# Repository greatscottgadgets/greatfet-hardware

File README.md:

# GreatFET Hardware

This repository is deprecated.  Please use the current GreatFET hardware design repositories located at:

https://github.com/greatfet-hardware

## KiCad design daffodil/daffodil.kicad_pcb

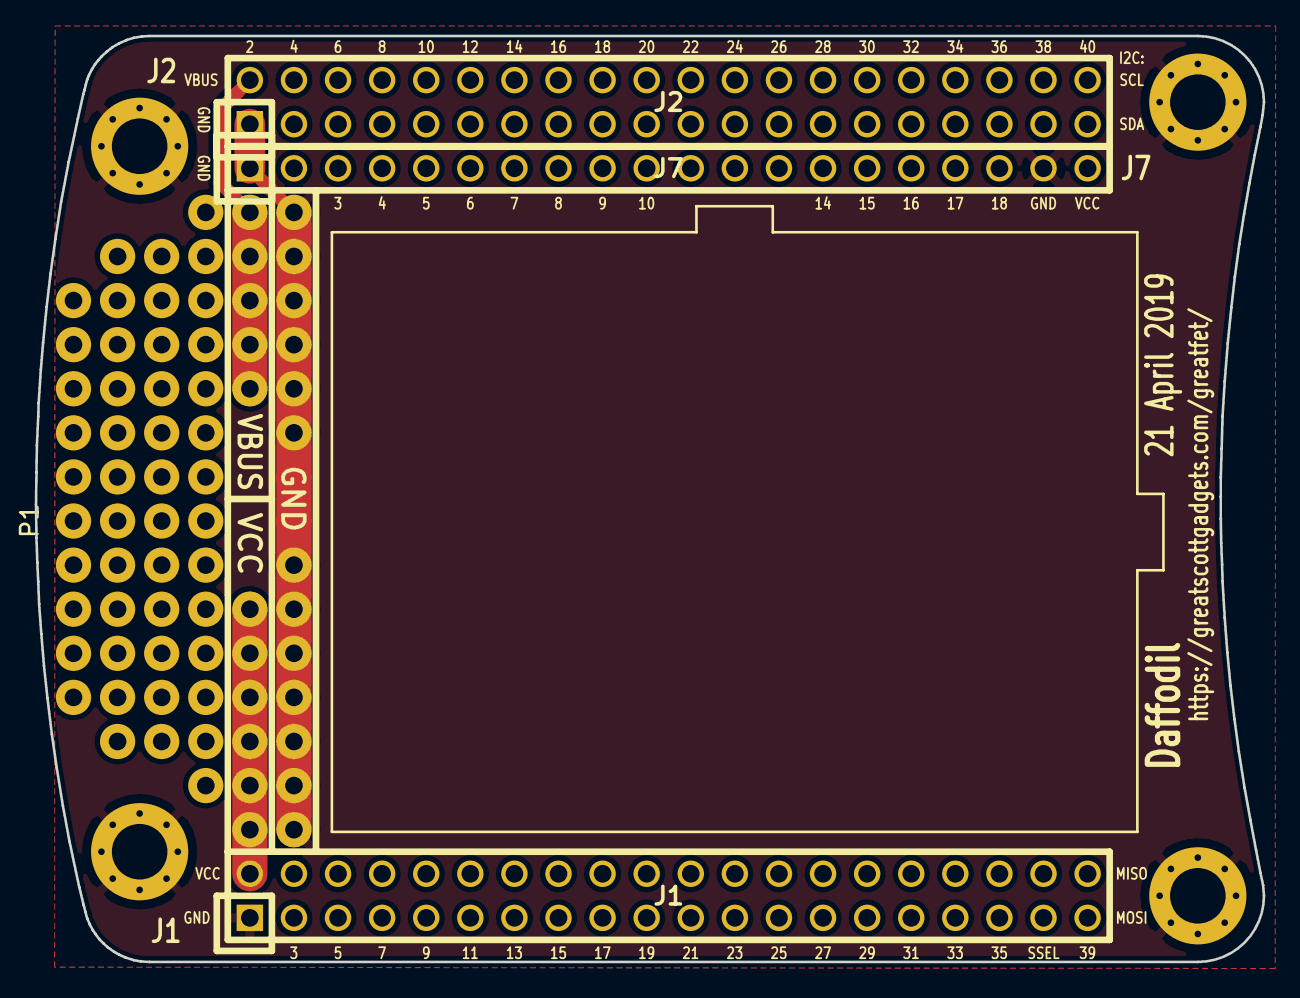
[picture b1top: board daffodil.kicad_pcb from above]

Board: 2 copper layers, 70.7 x 53.3 mm, 8 parts (0 on the bottom side), 3 nets.

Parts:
J1: NEIGHBOR1; HEADER-2x20
J2: NEIGHBOR2; HEADER-2x20
J7: BONUS_ROW; HEADER-1x20
MH1, MH2, MH3, MH4: MOUNTING_HOLE; HOLE126MIL-COPPER
P1: GREATFET-PROTO-AREA

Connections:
/VBUS: J2.2, P1.14, P1.15, P1.16, P1.17, P1.18
GND: J1.1, J2.1, J7.1, J7.19, MH1.1, MH2.1, MH3.1, MH4.1, P1.1, P1.2, P1.3, P1.4, P1.5, P1.6, P1.7, P1.8, P1.9, P1.10, P1.11, P1.12, P1.13
VCC: J1.2, J7.20, P1.19, P1.20, P1.21, P1.22, P1.23, P1.24

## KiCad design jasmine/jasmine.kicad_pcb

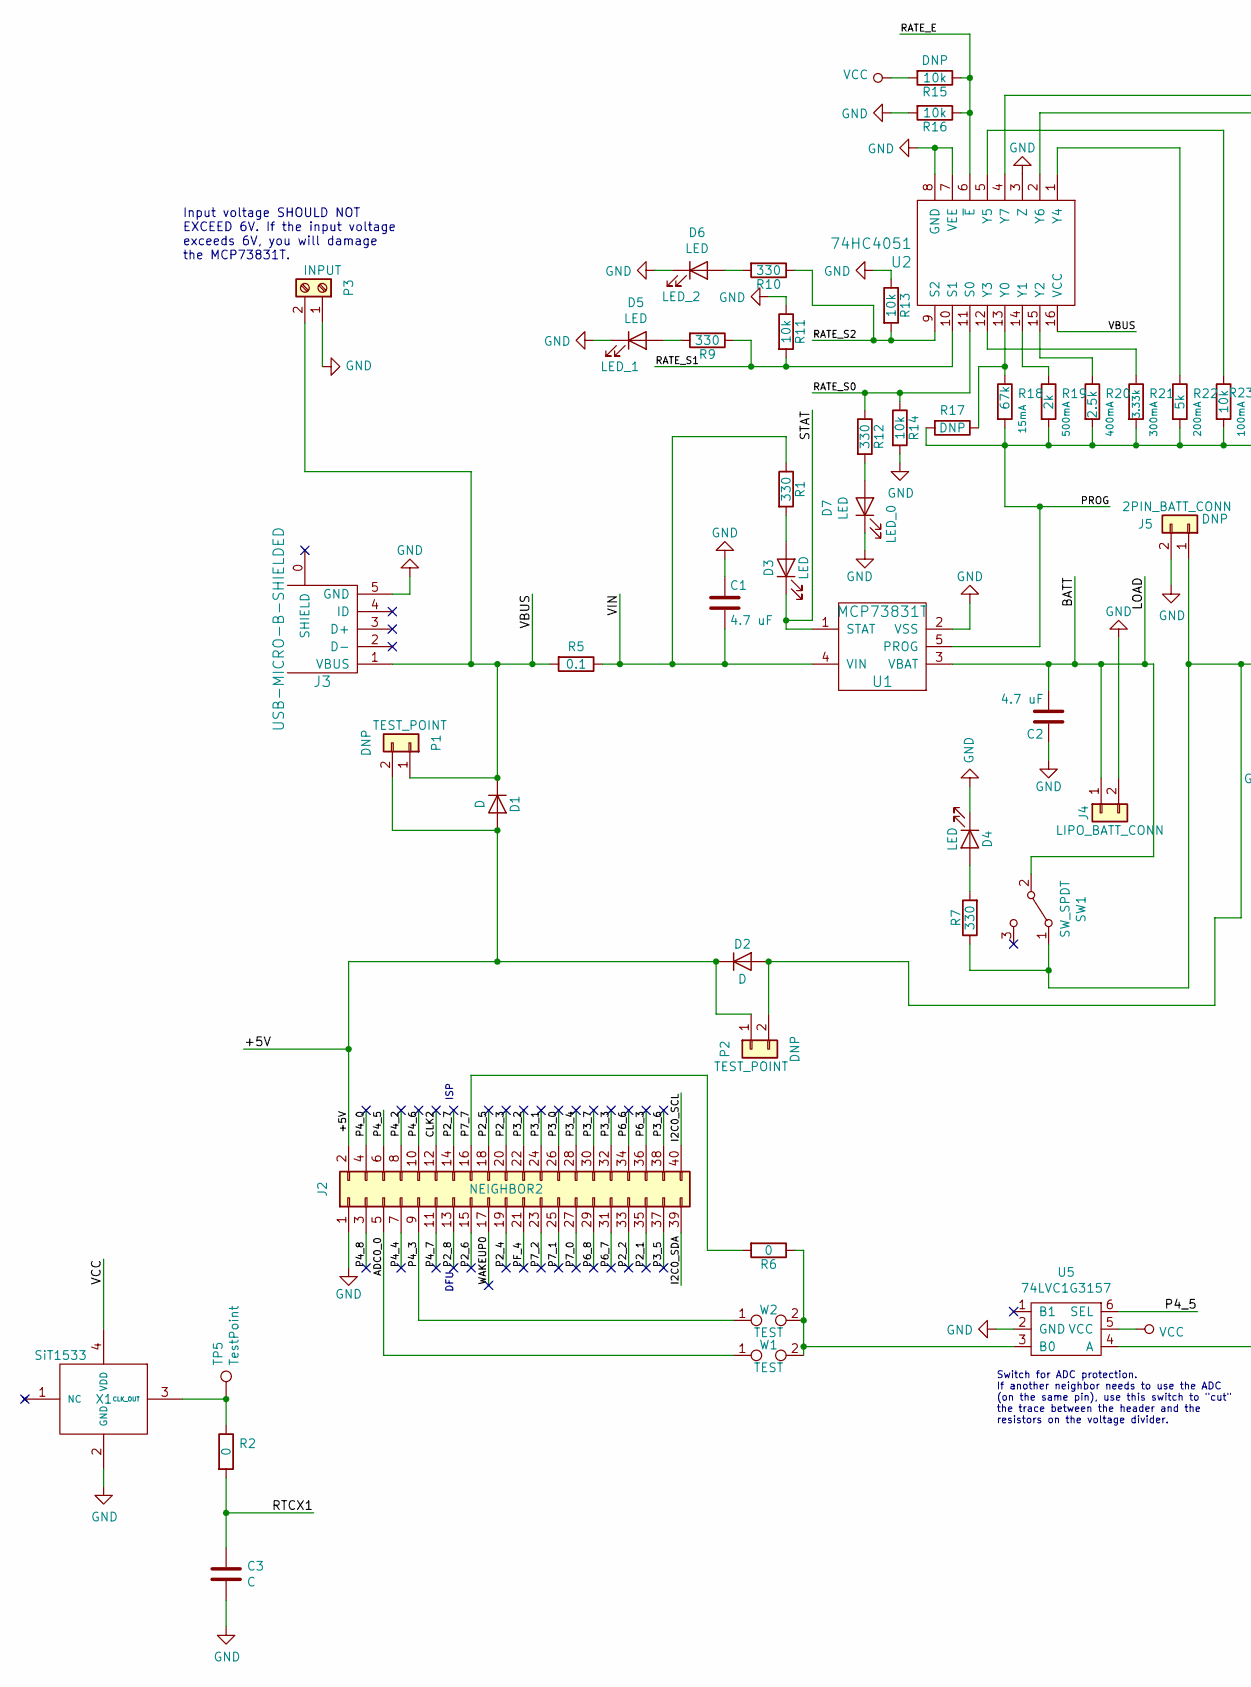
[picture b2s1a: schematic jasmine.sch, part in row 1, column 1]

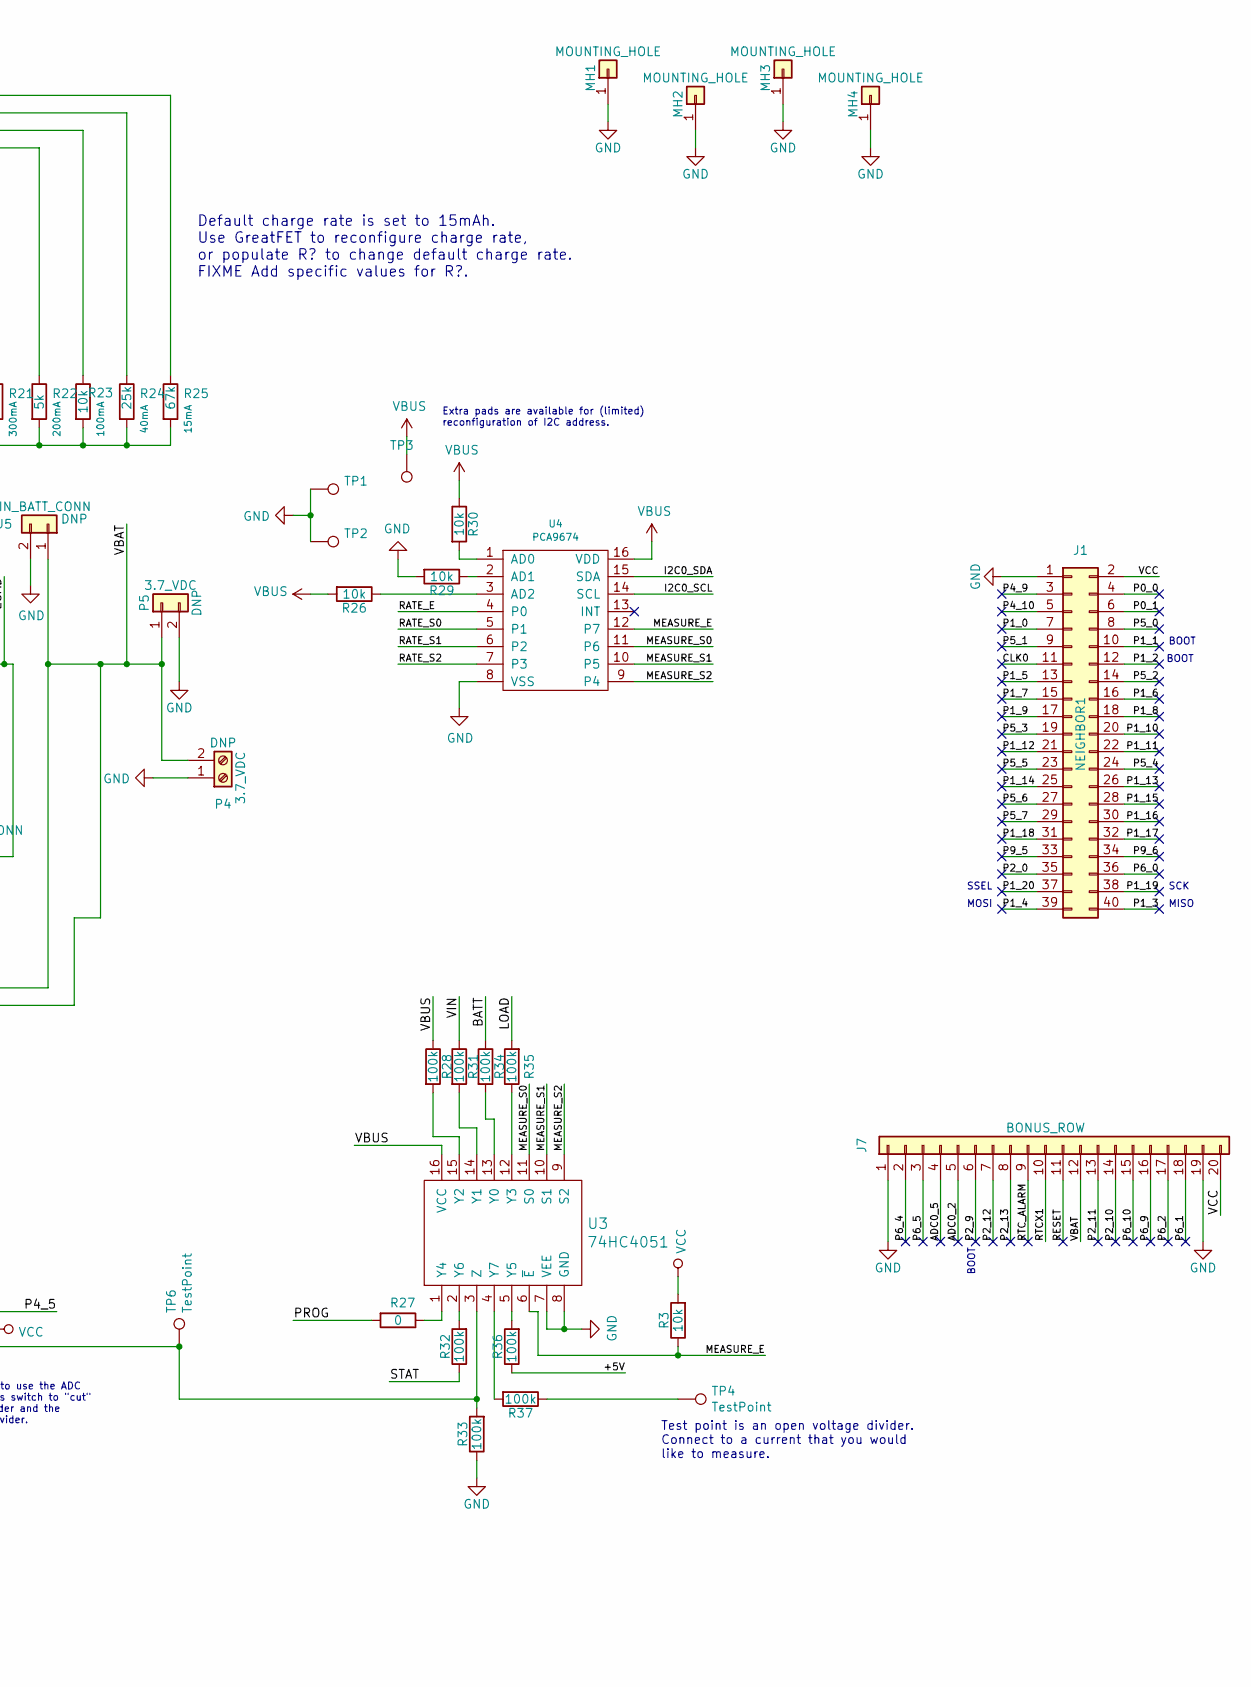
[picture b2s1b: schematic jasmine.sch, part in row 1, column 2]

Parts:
C1, C2: 4.7 uF; 0603; Part Number GRM188R60J475KE19D
C3: C; 0603
D1, D2: D; SOD128; Part Number PMEG3050EP,115
D3: LED; 0603D; Part Number SML-LX0603GW-TR
D4: LED; 0603D; Part Number SML-LX0603IW-TR
D5, D6, D7: LED; 0603D; Part Number SML-D12Y8WT86
J1: NEIGHBOR1; HEADER-2x20; Part Number SSQ-120-23-G-D
J2: NEIGHBOR2; HEADER-2x20; Part Number SSQ-120-23-G-D
J3: USB-MICRO-B-SHIELDED; USB-MICROB-FCI-10103592-LONGPADS; Part Number 10103592-0001LF
J4: LIPO_BATT_CONN; JST_PH_S2B-PH-SM4-TB_02x2.00mm_Angled; Part Number S2B-PH-SM4-TB(LF)(SN)
J5: 2PIN_BATT_CONN; JST_PH_S2B-PH-SM4-TB_02x2.00mm_Angled; Part Number S2B-PH-SM4-TB(LF)(SN)
J7: BONUS_ROW; HEADER-1x20; Part Number SSQ-120-23-G-S
MH1, MH2, MH3, MH4: MOUNTING_HOLE; HOLE126MIL-COPPER
P1, P2: TEST_POINT; HEADER-1x2; Part Number TSW-102-07-F-S
P3: INPUT; TerminalBlock_4UCON_19963_02x3.5mm_Straight; Part Number OSTTE020104
P4: 3.7_VDC; TerminalBlock_4UCON_19963_02x3.5mm_Straight; Part Number OSTTE020104
P5: 3.7_VDC; HEADER-1x2
R1, R9, R10, R12: 330; 0603; Part Number RMCF0603FT330R
R2, R27: 0; 0603; Part Number RMCF0603ZT0R00
R3, R11, R13, R14, R15, R16, R23, R26, R29, R30: 10k; 0603; Part Number RNCP0603FTD10K0
R5: 0.1; 0603; Part Number ERJ-3RSFR10V
R6: 0; 0603; Part Number RC0603JR-070RL
R7: 330; 0603; Part Number RMCF0603JT330R
R17: R; RESISTOR-AXIAL-2.3x6.0mm
R18, R25: 67k; 0603; Part Number RMCF0603FT66K5
R19: 2k; 0603; Part Number RMCF0603FT2K00
R20: 2.5k; 0603; Part Number RMCF0603FT2K49
R21: 3.33k; 0603; Part Number RMCF0603FG3K32
R22: 5k; 0603; Part Number RMCF0603FT4K99
R24: 25k; 0603; Part Number RMCF0603FT24K9
R28, R31, R32, R33, R34, R35, R36, R37: 100k; 0603; Part Number RMCF0603FG100K
SW1: SW_SPDT; MHSS1105; Part Number MHSS1105
TP1, TP2, TP3: 1Pin_0603
TP4, TP5, TP6: TestPoint; TESTPOINT-50MIL
U1: MCP73831T; SOT-23-5; Part Number MCP73831T-2ACI/OT
U2, U3: 74HC4051; SOIC16; Part Number 74HC4051D,653
U4: PCA9674; TSSOP16; Part Number PCA9674PW,118
U5: 74LVC1G3157; SOT363; Part Number 74LVC1G3157DW-7
W1, W2: TEST; 0603-JUMPER
X1: SiT1533; Part Number SIT1533AI-H4-AA2-32.768G

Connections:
/+5V: D1.2 (A), D2.1 (K), J2.2, P1.2, P2.1, R36.1
/ADC0_0: J2.5, W1.1
/ADC0_2: J7.5
/ADC0_5: J7.4
/BATT: C2.2, J4.1, R34.1, R35.2, SW1.2 (B), U1.3 (VBAT)
/CLK0: J1.11
/CLK2: J2.12
/I2C0_SCL: J2.40, U4.14 (SCL)
/I2C0_SDA: J2.39, U4.15 (SDA)
/MEASURE_E: R3.1, U3.6 (~E~), U4.12 (P7)
/MEASURE_S0: U3.11 (S0), U4.11 (P6)
/MEASURE_S1: U3.10 (S1), U4.10 (P5)
/MEASURE_S2: U3.9 (S2), U4.9 (P4)
/P0_0: J1.4
/P0_1: J1.6
/P1_0: J1.7
/P1_1: J1.10
/P1_2: J1.12
/P1_3: J1.40
/P1_4: J1.39
/P1_5: J1.13
/P1_6: J1.16
/P1_7: J1.15
/P1_8: J1.18
/P1_9: J1.17
/P1_10: J1.20
/P1_11: J1.22
/P1_12: J1.21
/P1_13: J1.26
/P1_14: J1.25
/P1_15: J1.28
/P1_16: J1.30
/P1_17: J1.32
/P1_18: J1.31
/P1_19: J1.38
/P1_20: J1.37
/P2_0: J1.35
/P2_1: J2.35
/P2_2: J2.33
/P2_3: J2.20
/P2_4: J2.19
/P2_5: J2.18
/P2_6: J2.15
/P2_7: J2.14
/P2_8: J2.13
/P2_9: J7.6
/P2_10: J7.14
/P2_11: J7.13
/P2_12: J7.7
/P2_13: J7.8
/P3_0: J2.26
/P3_1: J2.24
/P3_2: J2.22
/P3_3: J2.32
/P3_4: J2.28
/P3_5: J2.37
/P3_6: J2.38
/P3_7: J2.30
/P4_0: J2.4
/P4_2: J2.8
/P4_3: J2.9, W2.1
/P4_4: J2.7
/P4_5: J2.6, U5.6 (SEL)
/P4_6: J2.10
/P4_7: J2.11
/P4_8: J2.3
/P4_9: J1.3
/P4_10: J1.5
/P5_0: J1.8
/P5_1: J1.9
/P5_2: J1.14
/P5_3: J1.19
/P5_4: J1.24
/P5_5: J1.23
/P5_6: J1.27
/P5_7: J1.29
/P6_0: J1.36
/P6_1: J7.18
/P6_2: J7.17
/P6_3: J2.36
/P6_4: J7.2
/P6_5: J7.3
/P6_6: J2.34
/P6_7: J2.31
/P6_8: J2.29
/P6_9: J7.16
/P6_10: J7.15
/P7_0: J2.27
/P7_1: J2.25
/P7_2: J2.23
/P7_7: J2.16, R6.2
/P9_5: J1.33
/P9_6: J1.34
/PF_4: J2.21
/PROG: R17.2, R18.2, R19.2, R20.2, R21.2, R22.2, R23.2, R24.2, R25.2, R27.2, U1.5 (PROG)
/RATE_E: R15.1, R16.1, U2.6 (~E~), U4.4 (P0)
/RATE_S0: R12.1, R14.1, U2.11 (S0), U4.5 (P1)
/RATE_S1: R9.1, R11.2, U2.10 (S1), U4.6 (P2)
/RATE_S2: R10.1, R13.2, U2.9 (S2), U4.7 (P3)
/RESET: J7.11
/RTCX1: C3.1, J7.10, R2.2
/RTC_ALARM: J7.9
/STAT: D3.1 (K), R32.1, U1.1 (STAT)
/VBAT: D2.2 (A), J5.1, J7.12, P2.2, P4.2, P5.1, R7.1, SW1.1 (A)
/VIN: C1.2, R1.1, R5.1, R31.1, U1.4 (VIN)
/WAKEUP0: J2.17
GND: C1.1, C2.1, C3.2, D4.1 (K), D5.1 (K), D6.1 (K), D7.1 (K), J1.1, J2.1, J3.5 (GND), J4.2, J5.2, J7.1, J7.19, MH1.1, MH2.1, MH3.1, MH4.1, P3.1, P4.1, P5.2, R11.1, R13.1, R14.2, R16.2, R29.2, R33.1, TP1.1, TP2.1, U1.2 (VSS), U2.3 (Z), U2.7 (VEE), U2.8 (GND), U3.7 (VEE), U3.8 (GND), U4.8 (VSS), U5.2 (GND), X1.2 (GND)
unnamed: D3.2 (A), R1.2
unnamed: D4.2 (A), R7.2
unnamed: D5.2 (A), R9.2
unnamed: D6.2 (A), R10.2
unnamed: D7.2 (A), R12.2
unnamed: R2.1, TP5.1, X1.3 (CLK_OUT)
unnamed: R6.1, U5.3 (B0), W1.2, W2.2
unnamed: R17.1, R18.1, U2.13 (Y0)
unnamed: R19.1, U2.14 (Y1)
unnamed: R20.1, U2.15 (Y2)
unnamed: R21.1, U2.12 (Y3)
unnamed: R22.1, U2.1 (Y4)
unnamed: R23.1, U2.5 (Y5)
unnamed: R24.1, U2.2 (Y6)
unnamed: R25.1, U2.4 (Y7)
unnamed: R26.1, U4.3 (AD2)
unnamed: R27.1, U3.1 (Y4)
unnamed: R28.2, U3.15 (Y2)
unnamed: R29.1, U4.2 (AD1)
unnamed: R30.2, U4.1 (AD0)
unnamed: R31.2, U3.14 (Y1)
unnamed: R32.2, U3.2 (Y6)
unnamed: R33.2, TP6.1, U3.3 (Z), U5.4 (A)
unnamed: R34.2, U3.13 (Y0)
unnamed: R35.1, U3.12 (Y3)
unnamed: R36.2, U3.5 (Y5)
unnamed: R37.1, TP4.1
unnamed: R37.2, U3.4 (Y7)
VBUS: D1.1 (K), J3.1 (VBUS), P1.1, P3.2, R5.2, R26.2, R28.1, R30.1, TP3.1, U2.16 (VCC), U3.16 (VCC), U4.16 (VDD)
VCC: J1.2, J7.20, R3.2, R15.2, U5.5 (VCC), X1.4 (VDD)

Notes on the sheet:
MISO
MOSI
SCK
SSEL
ISP
DFU
BOOT
Default charge rate is set to 15mAh. Use GreatFET to reconfigure charge rate, or populate R? to change default charge rate. FIXME Add specific values for R?.
Extra pads are available for (limited) reconfiguration of I2C address.
Test point is an open voltage divider. Connect to a current that you would like to measure.
Switch for ADC protection. If another neighbor needs to use the ADC (on the same pin), use this switch to "cut" the trace between the header and the resistors on the voltage divider.
Input voltage SHOULD NOT EXCEED 6V. If the input voltage exceeds 6V, you will damage the MCP73831T.

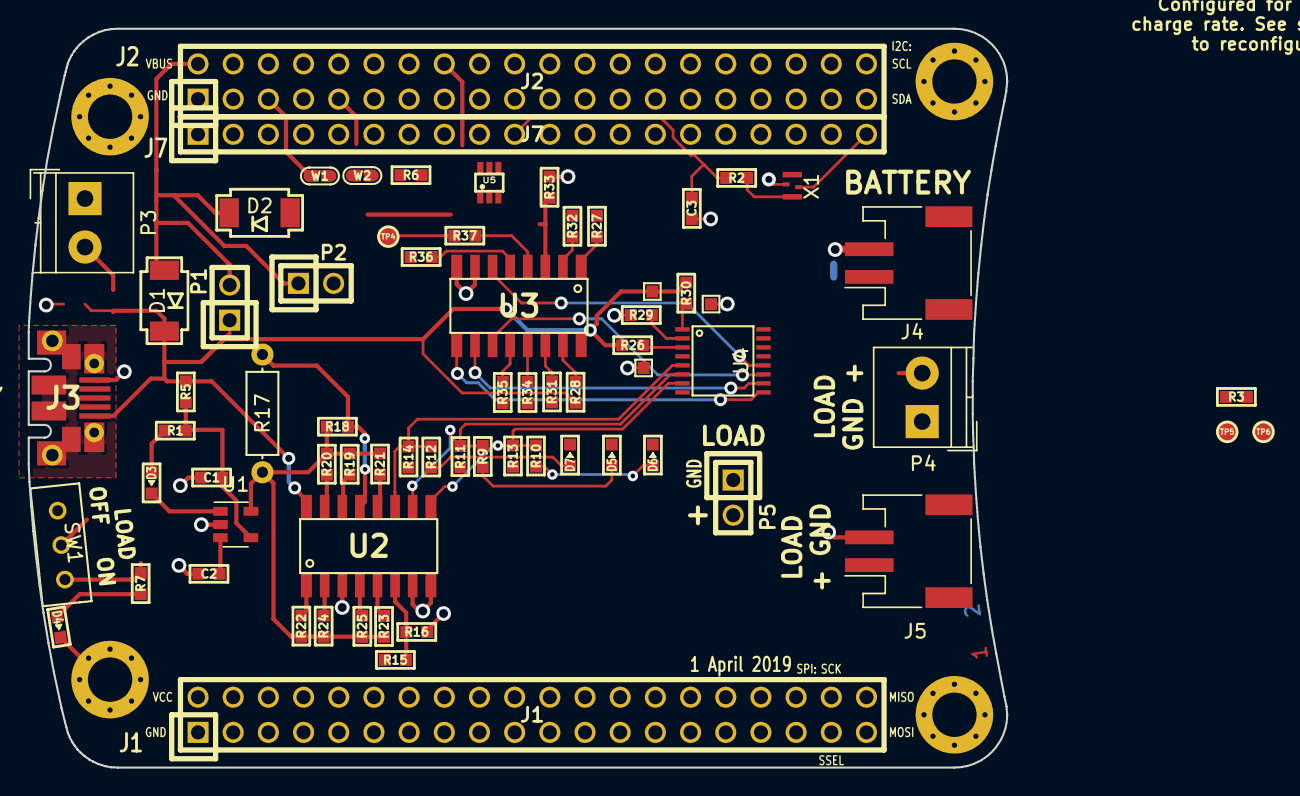
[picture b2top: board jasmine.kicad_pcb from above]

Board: 2 copper layers, 70.6 x 53.3 mm, 75 parts (0 on the bottom side), 52 nets.

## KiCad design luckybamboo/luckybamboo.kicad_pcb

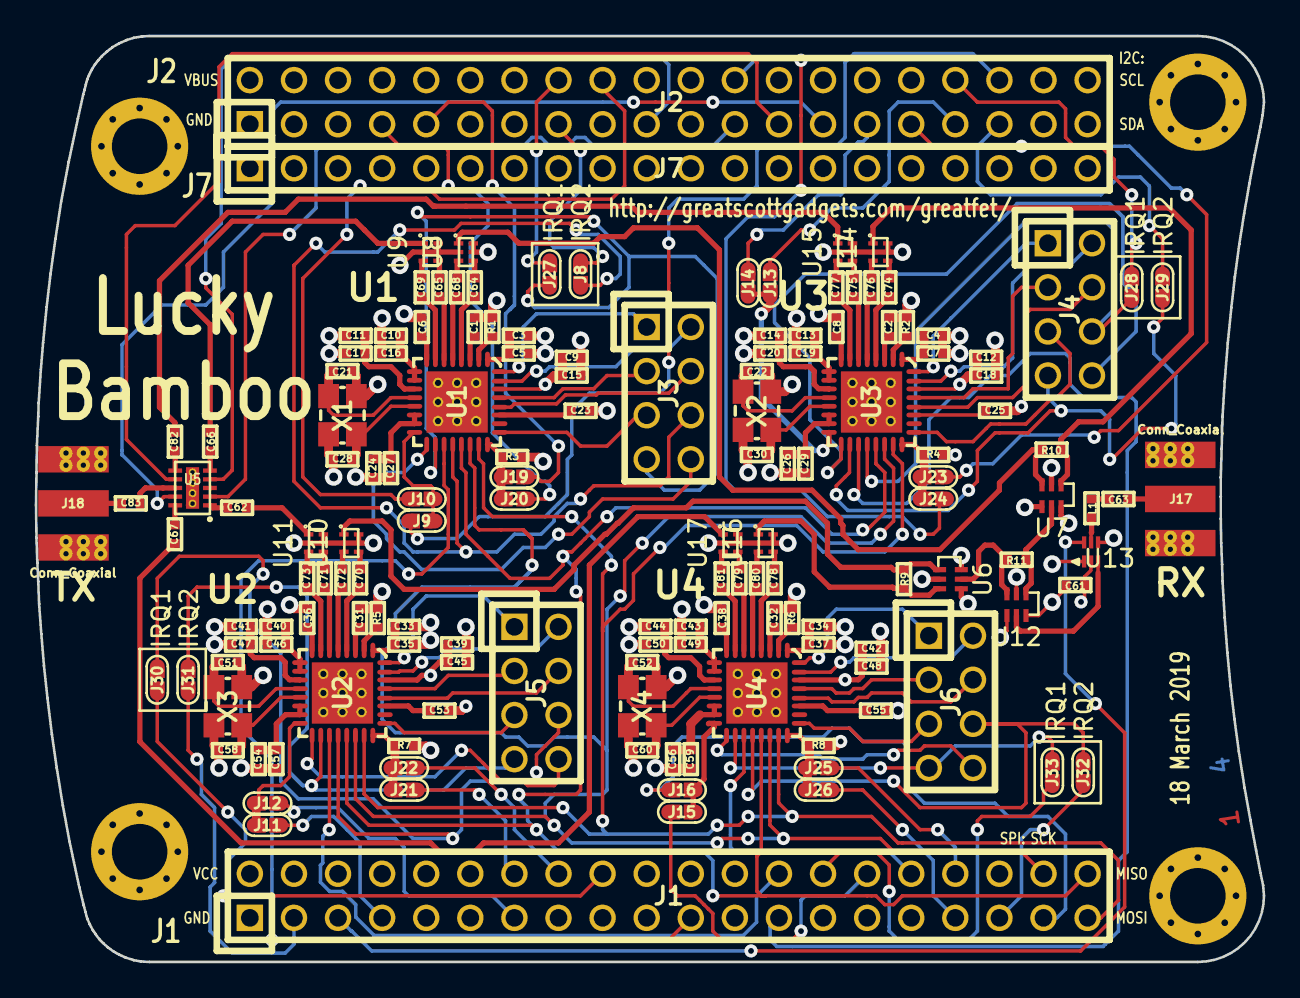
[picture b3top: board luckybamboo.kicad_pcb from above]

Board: 4 copper layers, 70.7 x 53.3 mm, 153 parts (0 on the bottom side), 170 nets.

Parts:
C1, C2, C6, C8, C31, C32, C36, C38: 100pF; 0402
C3, C4, C9, C10, C11, C12, C13, C14, C24, C26, C33, C34, C39, C40, C41, C42, C43, C44, C54, C56: 220nF; 0402
C5, C7, C15, C16, C17, C18, C19, C20, C27, C29, C35, C37, C45, C46, C47, C48, C49, C50, C57, C59: 27pF; 0402
C21, C22, C28, C30, C51, C52, C58, C60: 18pF; 0402
C23, C25, C53, C55, C61, C63: 1nF; 0402
C62, C66, C67, C82, C83: 47pF; 0402
C64, C65, C68, C69, C70, C71, C72, C73, C74, C75, C76, C77, C78, C79, C80, C81: 10nF; 0402
J1: NEIGHBOR1; HEADER-2x20
J2: NEIGHBOR2; HEADER-2x20
J3, J4, J5, J6: Conn_01x08; HEADER-2x4
J7: BONUS_ROW; HEADER-1x20
J8, J9, J10, J11, J12, J13, J14, J15, J16, J19, J20, J21, J22, J23, J24, J25, J26, J27, J28, J29, J30, J31, J32, J33: TEST_2P; 0603-JUMPER
J17, J18: Conn_Coaxial; SMA-EDGE
L1: 3.8nH; 0402
MH1, MH2, MH3, MH4: MOUNTING_HOLE; HOLE126MIL-COPPER
R1, R2, R5, R6: 27k; 0402
R3, R4, R7, R8: 10k; 0402
R9, R10, R11: 100; 0402
U1, U2, U3, U4: ADF7242; LFCSP32
U5: SKY13322; SKY13322-375LF
U6, U7, U12: HHM2293A1
U8, U9, U10, U11, U14, U15, U16, U17: ADF7242_balun
U13: BGA7H1N6
X1, X2, X3, X4: XTAL4PIN; XTAL3.2x2.5mm

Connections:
/DR1: J9.1, J10.1, U1.16
/DR2: J11.1, J12.1, U2.16
/DR3: J13.1, J14.1, U3.16
/DR4: J15.1, J16.1, U4.16
/DT1: J3.8, U1.17
/DT2: J5.8, U2.17
/DT3: J4.8, U3.17
/DT4: J6.8, U4.17
/IRQ1: J3.6, J8.2, U1.20
/IRQ2: J5.6, J30.2, U2.20
/IRQ3: J4.6, J28.2, U3.20
/IRQ4: J6.6, J32.2, U4.20
/P1_0: J1.7, J11.2
/P1_3: J1.40, U1.21, U2.21, U3.21, U4.21
/P1_4: J1.39, U1.23, U2.23, U3.23, U4.23
/P1_5: J1.13, J12.2
/P1_6: J1.16, J22.2
/P1_8: J1.18, J30.1
/P1_12: J1.21, U1.19
/P1_13: J1.26, U2.19
/P1_14: J1.25, U3.19
/P1_15: J1.28, J33.1
/P1_16: J1.30, J15.2
/P1_17: J1.32, U4.19
/P1_19: J1.38, U1.22, U2.22, U3.22, U4.22
/P1_20: J1.37, J16.2
/P2_0: J1.35, J32.1
/P2_1: J2.35, J29.1
/P2_2: J2.33, J13.2
/P2_4: J2.19, U5.4
/P2_5: J2.18, J10.2
/P2_6: J2.15, J8.1
/P3_1: J2.24, J24.2
/P4_3: J2.9, J19.2
/P4_4: J2.7, J20.2
/P4_9: J1.3, J31.1
/P4_10: J1.5, U13.6
/P5_2: J1.14, J21.2
/P6_3: J2.36, J9.2
/P6_6: J2.34, J28.1
/P6_7: J2.31, J23.2
/P6_8: J2.29, J14.2
/P7_0: J2.27, U5.9
/P7_1: J2.25, U5.7
/P7_2: J2.23, U5.2
/P7_7: J2.16, J27.1
/P9_5: J1.33, J26.2
/P9_6: J1.34, J25.2
/PABIAOP1: J3.1, U1.32
/PABIAOP2: J5.1, U2.32
/PABIAOP3: J4.1, U3.32
/PABIAOP4: J6.1, U4.32
/PAVSUP1: J3.2, U1.31
/PAVSUP2: J5.2, U2.31
/PAVSUP3: J4.2, U3.31
/PAVSUP4: J6.2, U4.31
/RFIN: L1.1, U13.5
/RFIN1: R10.1, U7.3, U8.1
/RFIN1_N: C68.2, U1.5
/RFIN1_P: C64.2, U1.4
/RFIN2: R9.2, U6.1, U10.1
/RFIN2_N: C72.2, U2.5
/RFIN2_P: C70.2, U2.4
/RFIN3: R10.2, U7.1, U14.1
/RFIN3_N: C76.2, U3.5
/RFIN3_P: C74.2, U3.4
/RFIN4: R9.1, U6.3, U16.1
/RFIN4_N: C80.2, U4.5
/RFIN4_P: C78.2, U4.4
/RFOUT1: C66.2, U9.1
/RFOUT1_N: C69.2, U1.7
/RFOUT1_P: C65.2, U1.6
/RFOUT2: C62.1, U11.1
/RFOUT2_N: C73.2, U2.7
/RFOUT2_P: C71.2, U2.6
/RFOUT3: C82.1, U15.1
/RFOUT3_N: C77.2, U3.7
/RFOUT3_P: C75.2, U3.6
/RFOUT4: C67.2, U17.1
/RFOUT4_N: C81.2, U4.7
/RFOUT4_P: C79.2, U4.6
/TRFS1: J3.7, J27.2, U1.18
/TRFS2: J5.7, J31.2, U2.18
/TRFS3: J4.7, J29.2, U3.18
/TRFS4: J6.7, J33.2, U4.18
/TXEN1: J3.5, U1.25
/TXEN2: J5.5, U2.25
/TXEN3: J4.5, U3.25
/TXEN4: J6.5, U4.25
/XOSC32KN1: J3.3, U1.29
/XOSC32KN2: J5.3, U2.29
/XOSC32KN3: J4.3, U3.29
/XOSC32KN4: J6.3, U4.29
/XOSC32KP1: J3.4, U1.28
/XOSC32KP2: J5.4, U2.28
/XOSC32KP3: J4.4, U3.28
/XOSC32KP4: J6.4, U4.28
/~CS~1: J19.1, J20.1, R3.2, U1.24
/~CS~2: J21.1, J22.1, R7.2, U2.24
/~CS~3: J23.1, J24.1, R4.2, U3.24
/~CS~4: J25.1, J26.1, R8.2, U4.24
GND: C1.1, C2.1, C3.1, C4.1, C5.1, C6.2, C7.1, C8.2, C9.1, C10.2, C11.2, C12.1, C13.2, C14.2, C15.1, C16.2, C17.2, C18.1, C19.2, C20.2, C21.2, C22.2, C23.1, C24.2, C25.1, C26.2, C27.2, C28.2, C29.2, C30.2, C31.1, C32.1, C33.1, C34.1, C35.1, C36.2, C37.1, C38.2, C39.1, C40.2, C41.2, C42.1, C43.2, C44.2, C45.1, C46.2, C47.2, C48.1, C49.2, C50.2, C51.2, C52.2, C53.1, C54.2, C55.1, C56.2, C57.2, C58.2, C59.2, C60.2, C61.1, J1.1, J2.1, J7.1, J7.10, J7.19, J17.2, J18.2, MH1.1, MH2.1, MH3.1, MH4.1, R1.1, R2.1, R5.1, R6.1, U1.0, U2.0, U3.0, U4.0, U5.0, U6.2, U6.4, U6.6, U7.2, U7.4, U7.6, U8.2, U8.5, U8.6, U9.2, U9.5, U9.6, U10.2, U10.5, U10.6, U11.2, U11.5, U11.6, U12.2, U12.4, U12.6, U13.1, U13.4, U14.2, U14.5, U14.6, U15.2, U15.5, U15.6, U16.2, U16.5, U16.6, U17.2, U17.5, U17.6, X1.2, X1.4, X2.2, X2.4, X3.2, X3.4, X4.2, X4.4
unnamed: C1.2, U1.3
unnamed: C2.2, U3.3
unnamed: C3.2, C5.2, U1.1
unnamed: C4.2, C7.2, U3.1
unnamed: C6.1, U1.8
unnamed: C8.1, U3.8
unnamed: C10.1, C16.1, U1.9, U1.10
unnamed: C11.1, C17.1, U1.11
unnamed: C13.1, C19.1, U3.9, U3.10
unnamed: C14.1, C20.1, U3.11
unnamed: C21.1, U1.12, X1.1
unnamed: C22.1, U3.12, X2.1
unnamed: C23.2, U1.27
unnamed: C24.1, C27.1, U1.14, U1.15
unnamed: C25.2, U3.27
unnamed: C26.1, C29.1, U3.14, U3.15
unnamed: C28.1, U1.13, X1.3
unnamed: C30.1, U3.13, X2.3
unnamed: C31.2, U2.3
unnamed: C32.2, U4.3
unnamed: C33.2, C35.2, U2.1
unnamed: C34.2, C37.2, U4.1
unnamed: C36.1, U2.8
unnamed: C38.1, U4.8
unnamed: C40.1, C46.1, U2.9, U2.10
unnamed: C41.1, C47.1, U2.11
unnamed: C43.1, C49.1, U4.9, U4.10
unnamed: C44.1, C50.1, U4.11
unnamed: C51.1, U2.12, X3.1
unnamed: C52.1, U4.12, X4.1
unnamed: C53.2, U2.27
unnamed: C54.1, C57.1, U2.14, U2.15
unnamed: C55.2, U4.27
unnamed: C56.1, C59.1, U4.14, U4.15
unnamed: C58.1, U2.13, X3.3
unnamed: C60.1, U4.13, X4.3
unnamed: C62.2, U5.1
unnamed: C63.1, L1.2
unnamed: C63.2, J17.1
unnamed: C64.1, U8.4
unnamed: C65.1, U9.4
unnamed: C66.1, U5.5
unnamed: C67.1, U5.10
unnamed: C68.1, U8.3
unnamed: C69.1, U9.3
unnamed: C70.1, U10.4
unnamed: C71.1, U11.4
unnamed: C72.1, U10.3
unnamed: C73.1, U11.3
unnamed: C74.1, U14.4
unnamed: C75.1, U15.4
unnamed: C76.1, U14.3
unnamed: C77.1, U15.3
unnamed: C78.1, U16.4
unnamed: C79.1, U17.4
unnamed: C80.1, U16.3
unnamed: C81.1, U17.3
unnamed: C82.2, U5.6
unnamed: C83.1, U5.8
unnamed: C83.2, J18.1
unnamed: R1.2, U1.2
unnamed: R2.2, U3.2
unnamed: R5.2, U2.2
unnamed: R6.2, U4.2
unnamed: R11.1, U6.5, U12.3
unnamed: R11.2, U7.5, U12.1
unnamed: U12.5, U13.3
VCC: C9.2, C12.2, C15.2, C18.2, C39.2, C42.2, C45.2, C48.2, C61.2, J1.2, J7.20, R3.1, R4.1, R7.1, R8.1, U1.30, U2.30, U3.30, U4.30, U13.2

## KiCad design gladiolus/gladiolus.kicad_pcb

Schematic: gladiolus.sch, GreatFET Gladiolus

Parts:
C1, C4: C; 0603
C2, C10, C26: 15pF; 0402; Part Number GRM1555C1H150GA01D
C3, C5, C6, C7, C11, C12, C13, C17, C18, C19, C20, C21, C22, C23, C24, C25, C27: 100nF; 0603; Part Number GRM188R71C104KA01D
C8: 10uF; 0805; Part Number GRM21BR61A106KE19L
C9: 100pF; 0402; Part Number GRM1555C1H101GA01D
C14: 130pF; 0402; Part Number GRM1555C1H131GA01D
C15: 82pF; 0402; Part Number GRM1555C1H820GA01D
C16: 24pF; 0402; Part Number GRM1555C1H240GA01D
C28: 8nF; 0603; Part Number GRM1555C1H150GA01D
C29: 470pF; 0402; Part Number GCM155R71H471KA37D
D1: PHOTODIODE; LED-3MM; Part Number PD204-6B
D2: PHOTODIODE; VBPW34FASR; Part Number VBPW34FASR
D3: LED; LED-5MM; Part Number TSHF5210
FB1: FILTER; 0805; Part Number BLM21PG221SN1D
J1: NEIGHBOR1; HEADER-2x20; Part Number SSQ-120-23-G-D
J2: NEIGHBOR2; HEADER-2x20; Part Number SSQ-120-23-G-D
J3: Conn_01x02_Female; HEADER-1x2
J7: BONUS_ROW; HEADER-1x20; Part Number SSQ-120-23-G-S
L1, L2, L5, L6, L7, L8: 2.2uH; 0402; Part Number MLF1005G2R2JT000
L3, L4: 1.5uH; 0402; Part Number MLF1005G1R5KT000
L9, L10: 1uH; 0402; Part Number MLF1005G1R0JT000
MH1, MH2, MH3, MH4: MOUNTING_HOLE; HOLE126MIL-COPPER
Q1: Q_NPN_BEC; SOT23-3; Part Number BSV52
R1, R2, R3, R4, R9, R19, R20, R21, R22, R23, R26, R29, R31, R38, R39, R40, R41, R42, R43, R44, R45, R64, R67, R72, R74, R77: 0; 0603; Part Number RC0603JR-070RL
R5, R11, R12, R13, R14, R37, R56: R; 0603
R6: 100k; 0402; Part Number RC0402FR-07100KL
R7: 3.24k; 0603; Part Number RC0603FR-073K24L
R8: 1.74k; 0603; Part Number RC0603FR-071K74L
R10, R27, R36, R55, R58, R59, R60, R61, R62, R63: 10k; 0603; Part Number ERJ-3GEYJ103V
R15, R16, R32, R33: 0; 0402; Part Number RC0402JR-070RL
R17, R18, R34, R35: R; 0402
R24, R25, R73: 1k; 0603; Part Number RC0603JR-071KL
R28, R46, R47, R48, R49, R50, R51, R52, R53, R54: 39; 0603; Part Number RC0603JR-0739RL
R30: 75; 0603; Part Number RC0603FR-0775RL
R57: 20k; 0603; Part Number RC0603JR-0720KL
R66, R69: 249; 0603; Part Number 311-249HR
R70: 1.80k; 0603; Part Number RC0603FR-071K8L
R71: 953; 0603; Part Number RC0603FR-07953RL
R75: 12k; 0603; Part Number RC0603JR-0712KL
R76: 1M; 0603
R78: 0; 0603
RV1, RV2, RV3: POT; 3306F; Part Number 3306F-1-103
U1: THS4520RGT; QFN16-3; Part Number THS4520RGT
U2: AD8330ARQZ; TSSOP16; Part Number AD8330ARQZ
U3: AD9283; SSOP20; Part Number AD9283BRSZ-50
U4: AD9704; QFN32-5; Part Number AD9704BCPZ
U5: LMH6643; VSSOP8; Part Number LMH6643MM
U6, U7: 74LVC1G3157; SOT363; Part Number 74LVC1G3157DW-7

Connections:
/ADC0_0: J2.5, R21.2, R64.2
/ADCCLK: R37.1, R46.1, U3.10
/D0: R38.2, U3.20
/D1: R39.2, U3.19
/D2: R40.2, U3.18
/D3: R41.2, U3.17
/D4: R42.2, U3.14
/D5: R43.2, U3.13
/D6: R44.2, U3.12
/D7: R45.2, U3.11
/DACCLK: R54.1, R56.1, U4.12
/P0_0: J1.4, R38.1
/P0_1: J1.6, R39.1
/P1_0: J1.7, R45.1
/P1_5: J1.13, R24.2
/P1_6: J1.16, R54.2
/P1_7: J1.15, R53.2
/P1_8: J1.18, R52.2
/P1_9: J1.17, R51.2
/P1_10: J1.20, R50.2
/P1_11: J1.22, R49.2
/P1_12: J1.21, R48.2
/P1_13: J1.26, R47.2
/P1_14: J1.25, R28.2
/P1_15: J1.28, R40.1
/P1_16: J1.30, R41.1
/P2_1: J2.35, R78.1
/P2_2: J2.33, R44.1
/P2_3: J2.20, R36.1, U3.1
/P2_5: J2.18, R9.2, R10.2, R19.1
/P3_5: J2.37, R77.2
/P4_3: J2.9, R29.2
/P4_4: J2.7, R22.2
/P4_8: J2.3, R26.2
/P5_0: J1.8, R55.2, U4.25, U7.6
/P5_2: J1.14, R58.2, R59.1, U4.15
/P5_3: J1.19, R60.2, R61.1, U4.16
/P5_5: J1.23, R62.2, R63.1, U4.17
/P5_6: J1.27, R25.2
/P6_3: J2.36, R42.1
/P6_6: J2.34, R43.1
/P9_6: J1.34, R46.2
/RXIN: C28.1, D1.2 (A), D2.2 (A), R5.1, R76.1, U6.4
/TXOUT: D3.1, Q1.3 (C)
/VBUS: J2.2, R3.2
GND: C1.2, C3.2, C5.2, C6.2, C7.2, C8.2, C11.2, C12.2, C13.2, C17.1, C18.1, C19.1, C20.1, C21.2, C22.2, C23.2, C24.1, C25.2, C27.2, J1.1, J2.1, J3.2, J7.1, J7.10, J7.19, MH1.1, MH2.1, MH3.1, MH4.1, R4.2, R8.1, R10.1, R14.2, R17.1, R18.2, R20.2, R27.2, R30.2, R34.1, R35.2, R37.2, R56.2, R57.1, R59.2, R61.2, R63.2, R66.2, R70.2, R76.2, RV1.1, RV2.1, RV3.1, U1.0, U1.13, U1.14, U1.15, U1.16, U2.8, U2.9, U2.11, U3.4, U3.9, U3.16, U4.0, U4.10, U4.14, U4.19, U4.22, U4.26, U5.4, U6.2, U7.2
unnamed: C1.1, D1.1 (K), D2.1 (K), R1.2, R2.1, R3.1, R4.1
unnamed: C2.1, L1.2, R6.1, U1.10
unnamed: C2.2, C28.2, R6.2, U1.11, U6.1
unnamed: C3.1, C4.2, R1.1, R7.1, R8.2, R11.1, R12.1, RV1.2, U1.2
unnamed: C4.1, L2.2, R11.2, U1.3
unnamed: C5.1, R5.2, U1.9
unnamed: C7.1, R12.2, R13.2, R14.1, U1.4
unnamed: C9.1, L1.1, L3.2
unnamed: C9.2, L2.1, L4.2
unnamed: C10.1, L3.1, R15.1
unnamed: C10.2, L4.1, R16.1
unnamed: C13.1, R31.1, U2.15
unnamed: C14.1, L5.1, L7.2
unnamed: C14.2, L6.1, L8.2
unnamed: C15.1, L7.1, L9.2
unnamed: C15.2, L8.1, L10.2
unnamed: C16.1, L9.1, R32.1
unnamed: C16.2, L10.1, R33.1
unnamed: C18.2, R31.2, U3.2, U3.3
unnamed: C24.2, R67.1, U4.23
unnamed: C25.1, R24.1, R25.1, R27.1, R67.2, U5.3, U7.1
unnamed: C26.1, R69.1, R70.1, R71.1, U5.2, U7.4
unnamed: C26.2, R71.2, R72.1, U5.1
unnamed: C29.1, R73.2, U5.7
unnamed: C29.2, R74.1, U5.6
unnamed: FB1.2, J1.2
unnamed: J3.1, Q1.2 (E), R30.1, R64.1, R74.2
unnamed: L5.2, U2.13
unnamed: L6.2, U2.12
unnamed: Q1.1 (B), R73.1
unnamed: R9.1, U1.12
unnamed: R15.2, R17.2, U2.4
unnamed: R16.2, R18.1, U2.5
unnamed: R19.2, U2.2
unnamed: R20.1, U2.1
unnamed: R21.1, R22.1, RV2.2, U2.7
unnamed: R23.1, R26.1, U2.6
unnamed: R28.1, U4.27
unnamed: R29.1, RV3.2, U2.10
unnamed: R32.2, R34.2, U3.6
unnamed: R33.2, R35.1, U3.7
unnamed: R47.1, U4.28
unnamed: R48.1, U4.29
unnamed: R49.1, U4.30
unnamed: R50.1, U4.31
unnamed: R51.1, U4.32
unnamed: R52.1, U4.1
unnamed: R53.1, U4.2
unnamed: R57.2, U4.24
unnamed: R66.1, U4.21
unnamed: R69.2, U4.20
unnamed: R72.2, U5.5
unnamed: R75.1, RV2.3
unnamed: R77.1, R78.2, U6.6
VCC: C6.1, C8.1, C11.1, C12.1, C17.2, C19.2, C20.2, C21.1, C22.1, C23.1, C27.1, D3.2, FB1.1, R2.2, R7.2, R13.1, R23.2, R36.2, R55.1, R58.1, R60.1, R62.1, R75.2, RV1.3, RV3.3, U1.5, U1.6, U1.7, U1.8, U2.3, U2.14, U2.16, U3.5, U3.8, U3.15, U4.3, U4.11, U4.18, U5.8, U6.5, U7.5

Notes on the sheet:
MISO
MOSI
SCK
SSEL
ISP
DFU
BOOT
10 MHz LPF
SGPIO0
SGPIO1
SGPIO2
SGPIO3
SGPIO4
SGPIO5
SGPIO6
SGPIO7
SGPIO8
GPIO1[0]
GPIO1[1]
GPIO1[2]
GPIO1[3]
GPIO1[4]
GPIO1[5]
GPIO1[6]
GPIO1[7]
GPIO1[9]
Default configuration: pin mode unsigned binary single-ended clock
GPIO1[8]
GPIO2[15]
GPIO2[12]
GPIO2[14]
GPIO2[11]
GPIO2[9]
switch for ac/dc coupling ac coupled on logic low
TODO: DNP?
short +/- inputs to turn off TX
removed DNP components for inverting output
^ This cap cuts off higher freqs (15MHz+) 470pF works well

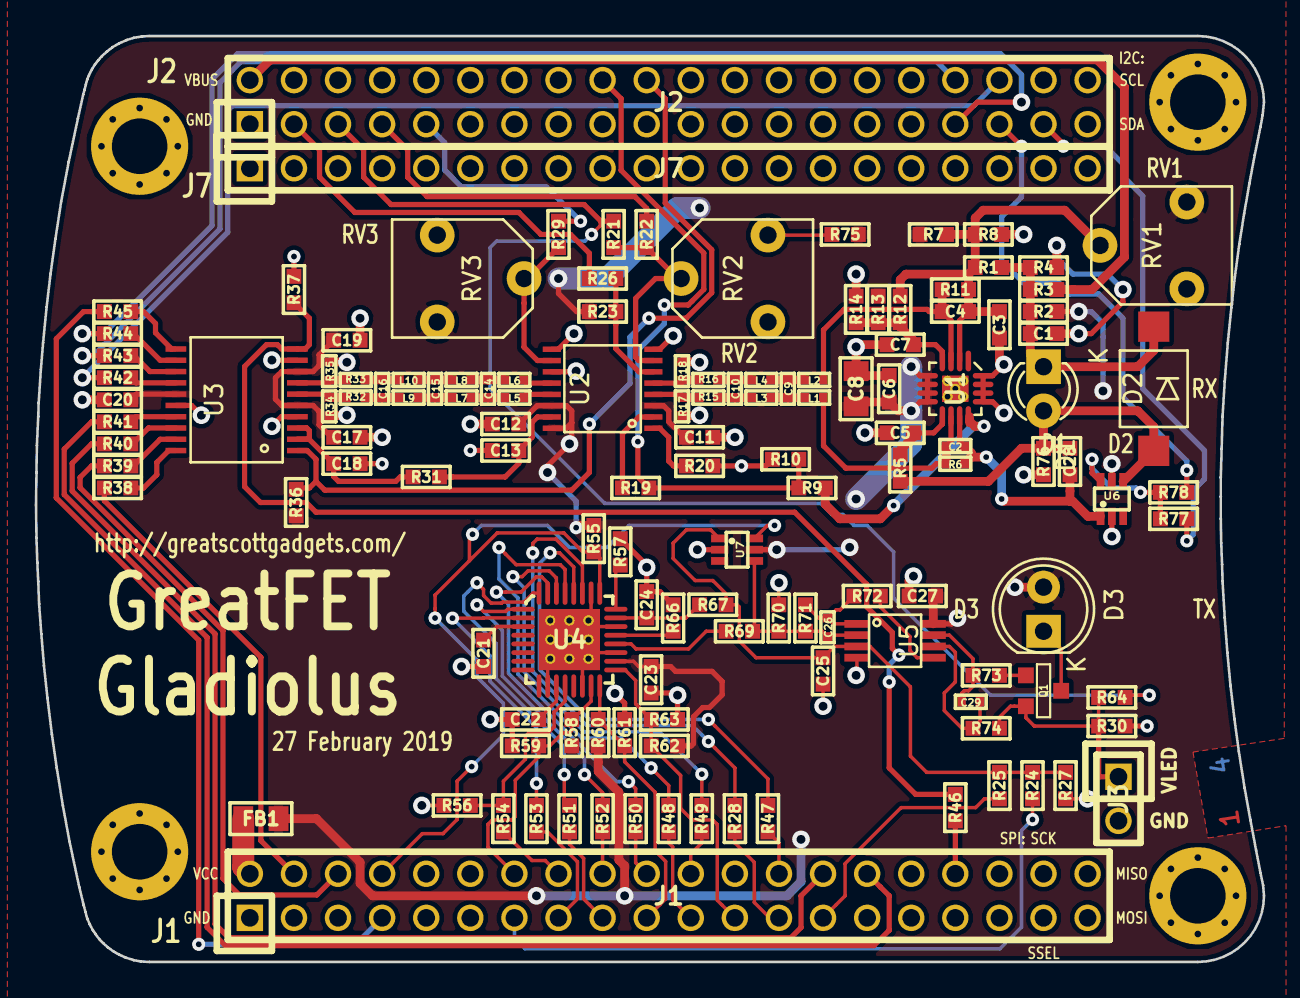
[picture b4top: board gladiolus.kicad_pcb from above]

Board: 4 copper layers, 70.7 x 53.3 mm, 138 parts (0 on the bottom side), 101 nets.

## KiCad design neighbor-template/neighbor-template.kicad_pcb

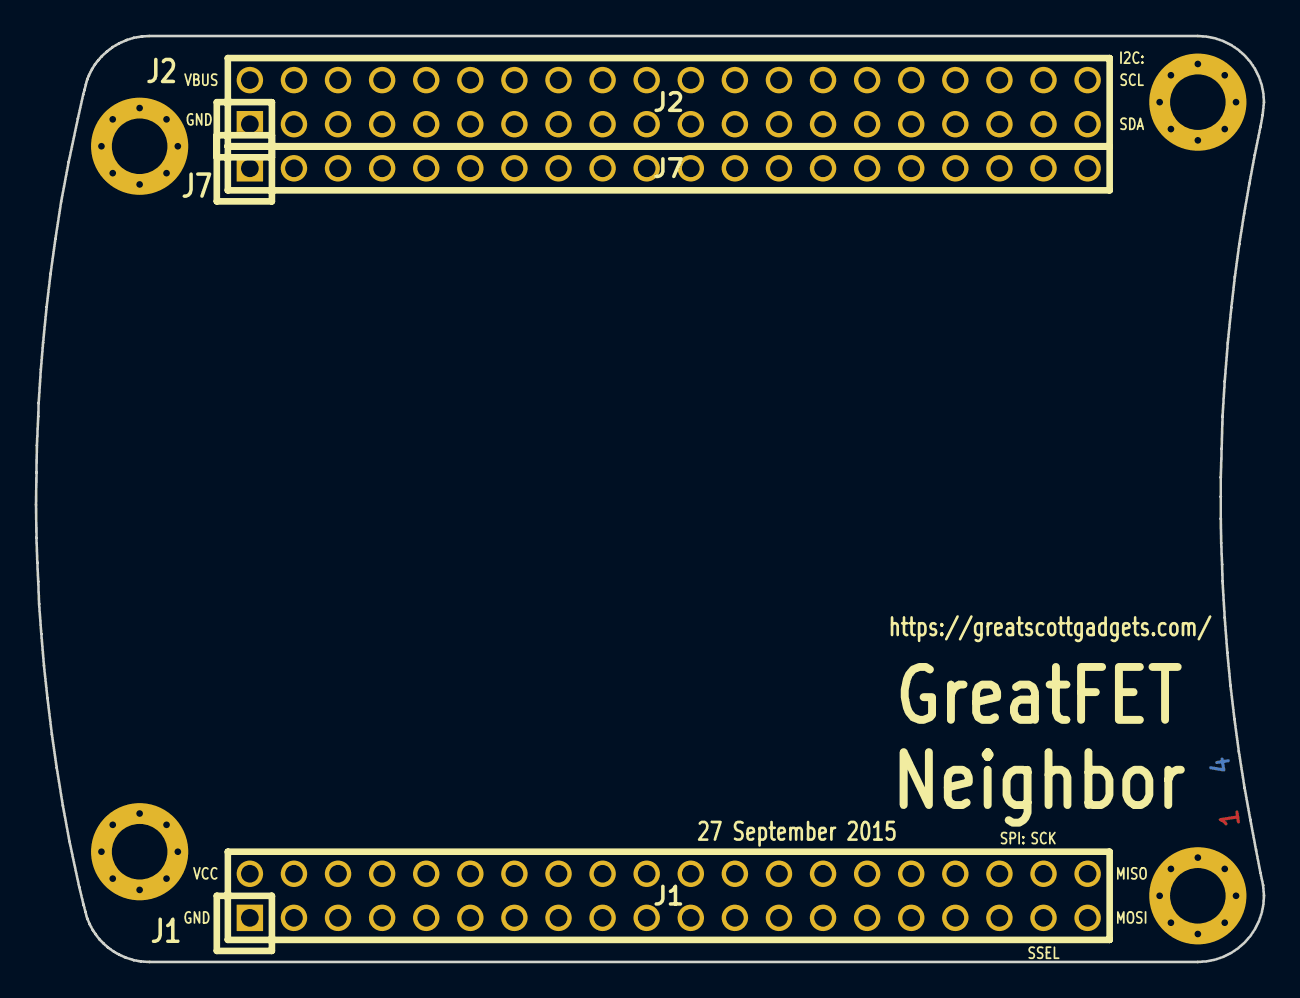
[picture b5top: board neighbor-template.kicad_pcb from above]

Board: 4 copper layers, 70.7 x 53.3 mm, 7 parts (0 on the bottom side), 2 nets, no tracks yet.

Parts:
J1: NEIGHBOR1; HEADER-2x20
J2: NEIGHBOR2; HEADER-2x20
J7: BONUS_ROW; HEADER-1x20
MH1, MH2, MH3, MH4: MOUNTING_HOLE; HOLE126MIL-COPPER

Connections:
GND: J1.1, J2.1, J7.1, J7.10, J7.19, MH1.1, MH2.1, MH3.1, MH4.1
VCC: J1.2, J7.20

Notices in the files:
azalea/azalea.kicad_pcb:
Copyright 2015-2018 Great Scott Gadgets
License: BSD-3-Clause
gladiolus/gladiolus.sch:
Copyright 2015 Michael Ossmann
License: GPL v2
narcissus/narcissus.kicad_pcb:
Copyright 2018 Great Scott Gadgets
